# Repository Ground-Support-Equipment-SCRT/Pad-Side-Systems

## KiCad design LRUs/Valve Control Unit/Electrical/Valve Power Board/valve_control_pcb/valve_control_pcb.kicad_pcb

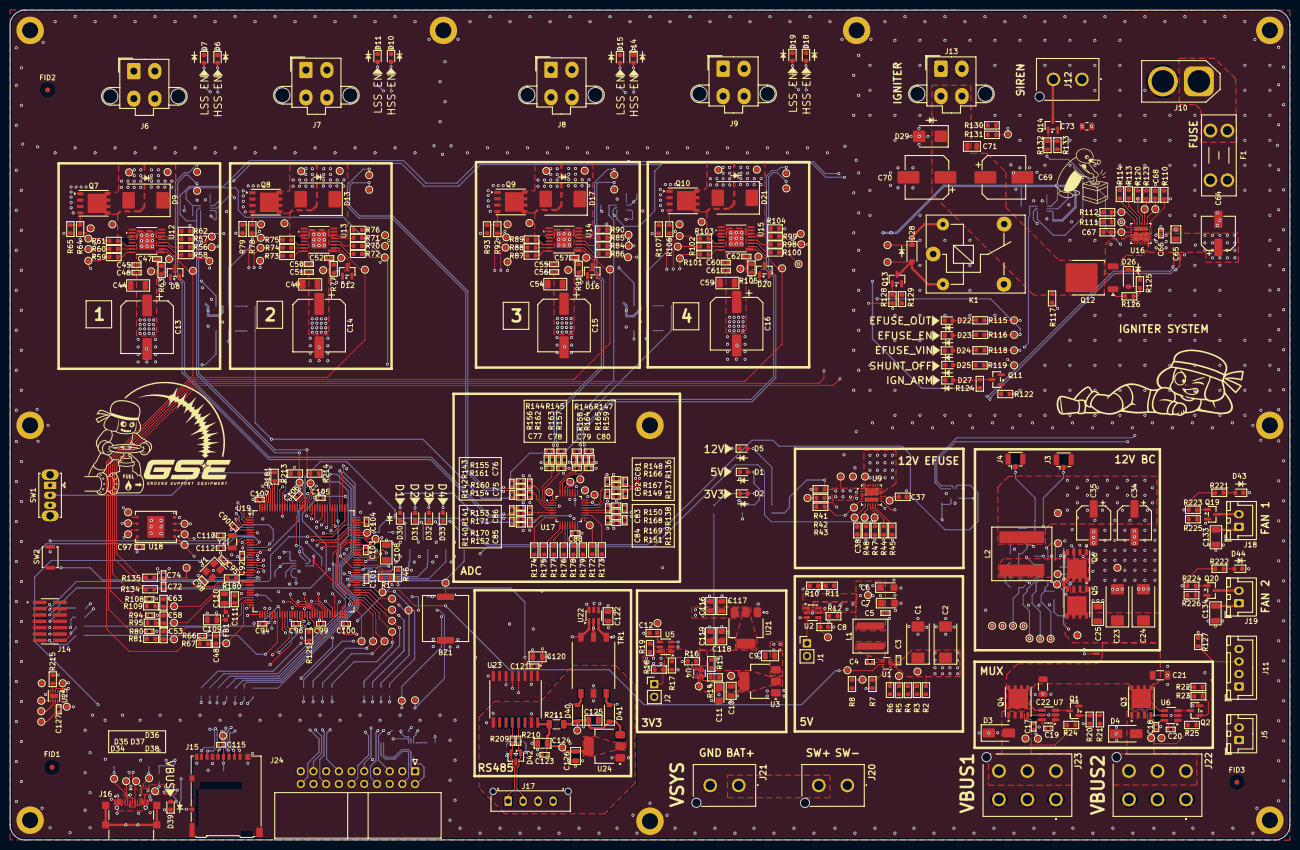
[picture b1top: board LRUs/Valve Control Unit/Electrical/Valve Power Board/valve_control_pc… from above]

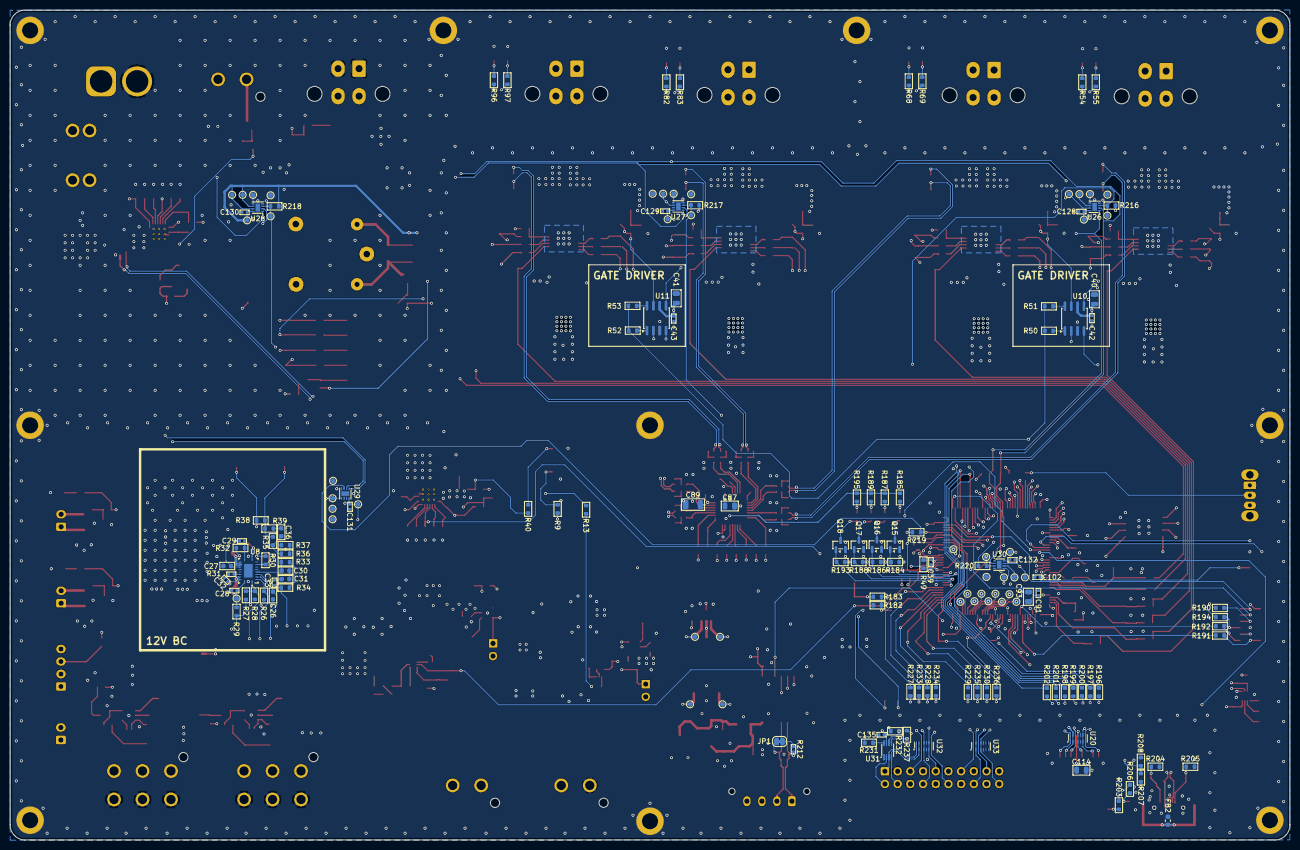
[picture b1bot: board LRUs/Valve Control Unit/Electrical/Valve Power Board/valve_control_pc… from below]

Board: 6 copper layers, 256.0 x 166.0 mm, 719 parts (162 on the bottom side), 374 nets.

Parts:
BZ1: Buzzer; Buzzer_Murata_PKMCS0909E
C1, C2, C23, C24: 10uF; CP_EIA-7343-31_Kemet-D
C3, C4, C5, C17, C18, C19, C20, C28, C32, C39, C42, C43, C45, C46, C47, C50, C51, C52, C55, C56, C57, C60, C61, C62, C66, C72, C74, C75, C76, C77, C78, C79, C80, C81, C82, C83, C84, C85, C86, C88, C90, C91, C92, C94, C96, C97, C99, C100, C101, C102, C103, C104, C105, C106, C107, C115, C121, C123, C127, C128, C129, C130, C131, C132, C135: 100nF; C_0402_1005Metric
C6, C7, C11: 10uF; CP_EIA-3216-18_Kemet-A
C8, C12, C37, C48, C53, C58, C63, C67, C111: 10nF; C_0603_1608Metric
C9, C10, C40, C41, C65, C71, C87, C93, C109, C110, C117, C118, C120: 1uF; C_0805_2012Metric
C13, C14, C15, C16: 120uF; CP_Elec_10x12.6
C21, C22, C25, C44, C49, C54, C59, C89, C108, C133, C134: 4.7uF; C_1206_3216Metric
C26, C38, C68: 47nF; C_0603_1608Metric
C27: 2.2uF; C_0603_1608Metric
C29, C33, C112, C113: 10pF; C_0402_1005Metric
C30, C31, C36: 330pF; C_0603_1608Metric
C34, C35, C64: 47uF; CP_Elec_6.3x5.4
C69, C70: 220uF; CP_Elec_8x10.5
C73, C114, C116, C119, C122, C124, C125, C126: 10uF; C_0805_2012Metric
C95, C98: 20pF; C_0402_1005Metric
D1, D2, D5, D6, D7, D10, D11, D14, D15, D18, D19, D43, D44: RED; LED_0603_1608Metric
D3, D4: SMAJ24A; D_SMA
D8, D12, D16, D20: BAS21; SOT-23
D9, D13, D17, D21: S3M-E3/57T; D_SMC
D22, D23, D24, D25, D27, D30, D31, D32, D33, D39: WHITE; LED_0603_1608Metric
D26: MMSZ5245B; D_SOD-123
D28: 1N4148WS; D_SOD-123
D29: SMBJ20A; D_SMB
D34, D35, D36, D37, D38: ESD441; X2SON2_DPL_TEX
D40, D41: MBR0520LT1G; D_SOD-123
D42: SM712_SOT23; SOT-23
F1: 0297020; Fuseholder_Blade_Mini_Keystone_3568
FB1, FB2: 120R; L_0603_1608Metric
FID1, FID2, FID3: Fiducial; Fiducial_1mm_Mask3mm
H1, H2, H3, H4, H5, H6, H7, H8, H9, H10: MountingHole_Pad; MountingHole_3.2mm_M3_ISO14580_Pad
J1: 01x02_PinHeader; PinHeader_1x02_P2.54mm_Vertical
J2: Conn_01x02_Pin; PinHeader_1x02_P2.54mm_Vertical
J3, J4: Conn_Coaxial; U.FL_Hirose_U.FL-R-SMT-1_Vertical
J5, J18, J19: B2B-XH-A; JST_XH_B2B-XH-A_1x02_P2.50mm_Vertical
J6, J7, J8, J9, J13: 0039299047; Molex_Mini-Fit_Jr_5566-04A2_2x02_P4.20mm_Vertical
J10: XT-60; AMASS_XT60-M_1x02_P7.20mm_Vertical
J11: B4B-XH-A; JST_XH_B4B-XH-A_1x04_P2.50mm_Vertical
J12, J20, J21: 0768290102; 768290102
J14: Conn_ST_STDC14; SAMTEC_FTSH-107-01-X-DV-K
J15: Micro_SD_Card_Det2; microSD_HC_Hirose_DM3AT-SF-PEJM5
J16: GSB1C41110SSHR; AMPHENOL_GSB1C41110SSHR
J17: 0436500415; Molex_Micro-Fit_3.0_43650-0415_1x04_P3.00mm_Vertical
J22, J23: 0768290106; 768290106
J24: IDC-Header_2x10; IDC-Header_2x10_P2.54mm_Horizontal
JP1: SolderJumper_2_Bridged; SolderJumper-2_P1.3mm_Bridged_RoundedPad1.0x1.5mm
K1: J107F1CS205VDC.45; Relay_SPDT_SANYOU_SRD_Series_Form_C
L1: 15uH; L_Coilcraft_XAL6060-XXX
L2: 4.7uH; L_Coilcraft_XAL1010-XXX
NT1, NT2: NetTie_2; NetTie-2_SMD_Pad0.5mm
Q1, Q2, Q11, Q13, Q14, Q15, Q16, Q17, Q18, Q19, Q20: AO3400A; SOT-23
Q3, Q4, Q5, Q6, Q7, Q8, Q9, Q10: SIR5108DP; PowerPAK_SO-8_Single
Q12: STD52P3LLH6; TO-252-2
R1, R16, R125, R129, R132, R184, R186, R188, R193, R225, R226: 47k; R_0603_1608Metric
R2: 220k; R_0603_1608Metric
R3, R14, R26, R30: 20k; R_0603_1608Metric
R4, R47, R120: 9.1k; R_0603_1608Metric
R5, R11: 51k; R_0603_1608Metric
R6, R44, R45, R50, R51, R52, R53, R113, R114, R172, R173, R174, R175, R176, R177, R178, R179, R190, R191, R192, R194, R196, R197, R198, R200, R201, R202, R227, R228, R229, R230, R233, R234, R235, R236: 0; R_0603_1608Metric
R7, R27, R112: 68k; R_0603_1608Metric
R8: 13k; R_0603_1608Metric
R9, R206: 2k; R_0603_1608Metric
R10, R17: 150k; R_0603_1608Metric
R12, R15, R19, R40, R46, R62, R65, R76, R79, R90, R93, R104, R107, R110, R115, R118, R121, R133, R181, R203: 10k; R_0603_1608Metric
R13: 220; R_0603_1608Metric
R18, R21, R23, R24, R25, R43, R117, R131, R207: 100k; R_0603_1608Metric
R20, R22, R49, R122, R134, R135: 1k; R_0603_1608Metric
R28: 8.2k; R_0603_1608Metric
R29: 2; R_0603_1608Metric
R31, R209, R210: 10; R_0402_1005Metric_GSE
R32: 680; R_0603_1608Metric
R33, R48, R64, R78, R92, R106, R123, R126, R128, R183, R223, R224: 100; R_0603_1608Metric
R34: 1.8k; R_0603_1608Metric
R35: 18k; R_0603_1608Metric
R36: 1.2k; R_0603_1608Metric
R37, R39: 75; R_0603_1608Metric
R38: 10; R_0603_1608Metric
R41, R111, R182: 1M; R_0603_1608Metric
R42: 22k; R_0603_1608Metric
R54, R55, R63, R68, R69, R77, R82, R83, R91, R96, R97, R105, R185, R187, R189, R195, R213, R214, R215, R216, R217, R218, R219, R220, R232, R237: 4.7k; R_0603_1608Metric
R56, R57, R58, R59, R60, R61, R67, R70, R71, R72, R73, R74, R75, R81, R84, R85, R86, R87, R88, R89, R95, R98, R99, R100, R101, R102, R103, R109: 15k; R_0603_1608Metric
R66, R80, R94, R108: 680; R_0402_1005Metric_GSE
R116, R119, R124, R127, R221, R222: 2.2k; R_0603_1608Metric
R130: 510k; R_0603_1608Metric
R136, R137, R138, R139, R140, R141, R142, R143, R144, R145, R146, R147: 15k; R_0402_1005Metric_GSE
R148, R149, R150, R151, R152, R153, R154, R155, R156, R157, R158, R159: 90.9k; R_0402_1005Metric_GSE
R160, R161, R162, R163, R164, R165, R166, R167, R168, R169, R170, R171: 1k; R_0402_1005Metric_GSE
R180: 390; R_0603_1608Metric
R199: 22; R_0603_1608Metric
R204, R205: 5.1k; R_0603_1608Metric
R208, R231: 200k; R_0603_1608Metric
R211: 0; R_1206_3216Metric
R212: 120; R_0402_1005Metric_GSE
SW1: SW_SPDT; SW_Slide_SPDT_Straight_CK_OS102011MS2Q
SW2: SW_Push; SW_Push_SPST_NO_Alps_SKRK
TP1, TP2, TP3, TP4, TP5, TP6, TP7, TP8, TP9, TP10, TP11, TP12, TP13, TP14, TP15, TP16, TP17, TP18, TP19, TP20, TP21, TP22, TP23, TP24, TP25, TP26, TP27, TP28, TP29, TP30, TP31, TP32, TP33, TP34, TP35, TP36, TP37, TP38, TP39, TP40, TP41, TP42, TP43, TP44, TP45, TP46, TP47, TP48, TP49, TP50, TP51, TP52, TP53, TP54, TP55, TP56, TP57, TP58, TP59, TP60, TP61, TP62, TP63, TP64, TP65, TP66, TP67, TP68, TP69, TP70, TP71, TP72, TP73, TP74, TP75, TP76, TP77, TP78, TP79, TP80, TP81, TP82, TP83, TP84, TP85, TP86, TP87, TP88, TP89, TP90, TP91, TP92, TP93, TP94, TP95, TP96, TP97, TP98, TP99, TP100, TP101, TP102, TP103, TP104, TP105, TP106, TP107, TP108, TP109, TP110, TP111, TP112, TP113, TP114, TP115, TP116, TP117, TP118, TP119, TP120, TP121, TP122, TP123, TP124, TP125, TP126, TP127, TP128, TP129, TP130, TP131, TP132, TP133, TP134, TP135, TP136, TP137, TP138, TP139, TP140, TP141, TP142, TP143, TP144, TP145, TP146, TP147, TP148, TP149, TP150, TP151, TP152, TP153, TP154, TP155, TP156, TP157, TP158, TP159, TP160, TP161, TP162, TP163, TP164, TP165, TP166, TP167, TP168, TP169, TP170, TP171, TP172, TP173, TP174, TP175, TP176, TP177, TP178, TP179, TP180, TP181, TP182, TP183, TP184, TP185, TP186, TP187, TP188, TP189, TP190, TP191, TP192, TP193, TP194, TP195, TP196, TP197, TP198: TestPoint; TestPoint_Pad_D1.0mm
TR1: 750315371; Transformer_Wuerth_750315371
U1: TPS62933P; SOT-583-8
U2, U5: TPS22810DBV; SOT-23-6
U3, U21: AMS1117-3.3; SOT-223-3_TabPin2
U4: TPS2116DRL; SOT-583-8
U6, U7: LM74700; SOT-23-6_Handsoldering
U8: LM5145RGYR
U9: TPS259830; IC_TPS259830ONRGER
U10, U11: UCC27524D; SOIC-8_3.9x4.9mm_P1.27mm
U12, U13, U14, U15: TPS27SA08CPWPR; TSSOP_CPWPR_TEX
U16: TPS259830ONRGER; IC_TPS259830ONRGER
U17: ADS124S08IPBSR; QFP50P700X700X120-32N
U18: W25Q128JVE; WSON-8-1EP_8x6mm_P1.27mm_EP3.4x4.3mm
U19: STM32L496ZGT6; LQFP-144_20x20mm_P0.5mm
U20, U32, U33: TPD6E05U06RVZ; Texas_R-PUSON-N14
U22: SN6505BDBVR; SOT-23-6
U23: ISO1450BDWR; SOIC127P1030X265-16N
U24: AMS1117-5.0; SOT-223-3_TabPin2
U25, U26, U27, U28, U29, U30: TMP1075DSGR; Texas_DSG0008A_WSON-8-1EP_2x2mm_P0.5mm_EP0.9x1.6mm
U31: PCA9306DC1Z; VSSOP-8_2.3x2mm_P0.5mm
Y1: 8MHz; Crystal_SMD_3225-4Pin_3.2x2.5mm
Y2: 32KHz; Crystal_SMD_3215-2Pin_3.2x1.5mm

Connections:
3V3_EXT: J24.2, U31.2 (VREF1)
3V3_STATUS: R16.2, U4.8 (ST), U19.15 (PF5)
3V3_USB: C118.1, C119.1, U4.6 (VIN2), U21.2 (VO)
5V_MAIN_PG: R1.2, TP1.1 (1_1), U1.7 (PG), U19.89 (PG4)
+3V3: C88.1, C90.1, C92.1, C94.1, C96.1, C97.1, C99.1, C100.1, C101.1, C103.1, C104.1, C105.1, C106.1, C107.1, C108.1, C109.1, C114.1, C115.1, C120.1, C121.1, C127.1, C128.1, C129.1, C130.1, C131.1, C132.1, C135.1, FB1.1, J14.3 (VCC), J15.4 (VDD), R1.1, R19.2, R46.1, R62.1, R76.1, R90.1, R104.1, R121.1, R124.1, R203.1, R213.2, R214.2, R215.2, R216.2, R217.2, R218.2, R219.2, R220.2, R231.2, R232.2, R237.2, SW1.3 (C), TP134.1 (1_1), TP153.1 (1_1), TP155.1 (1_1), TP159.1 (1_1), TP162.1 (1_1), TP165.1 (1_1), TP167.1 (1_1), TP168.1 (1_1), TP171.1 (1_1), TP175.1 (1_1), TP177.1 (1_1), TP179.1 (1_1), TP181.1 (1_1), TP183.1 (1_1), U5.6 (VOUT), U17.15 (IOVDD), U17.16 (DVDD), U18.8 (VCC), U19.6 (VBAT), U19.17 (VDD), U19.39 (VDD), U19.52 (VDD), U19.62 (VDD), U19.72 (VDD), U19.84 (VDD), U19.95 (VDDIO2), U19.106 (VDDUSB), U19.108 (VDD), U19.121 (VDD), U19.131 (VDDIO2), U19.144 (VDD), U23.1 (VCC1), U25.8 (V+), U26.7 (A0), U26.8 (V+), U27.6 (A1), U27.8 (V+), U28.6 (A1), U28.7 (A0), U28.8 (V+), U29.5 (A2), U29.8 (V+), U30.5 (A2), U30.7 (A0), U30.8 (V+), U31.7 (VREF2)
+5V: C40.1, C41.1, C42.1, C43.1, C87.1, C122.1, D28.1 (K), K1.5, R12.2, R185.2, R187.2, R189.2, R195.2, TP108.1 (1_1), TR1.2, U2.6 (VOUT), U10.6 (V_{DD}), U11.6 (V_{DD}), U17.26 (AVDD), U22.2 (VCC), U22.5 (EN)
+12V: C34.1, C35.1, C73.1, C133.1, C134.1, J3.1 (In), J12.1, J18.1, J19.1, L2.2, R38.2, R40.1, R41.2, TP23.1 (1_1), TP24.1 (1_1), U9.1 (IN), U9.2 (IN), U9.3 (IN), U9.16 (IN), U9.25 (IN), U9.27 (EPAD), U9.28 (EPAD), U9.29 (EPAD), U9.30 (EPAD), U9.31 (EPAD), U9.32 (EPAD)
/ADC/AINCOM: TP112.1 (1_1), U17.1 (AINCOM)
/ADC/CLK: R172.2, TP114.1 (1_1), U17.17 (CLK)
/ADC/IGN_VSENSE_DIV_N: R137.1, R149.2, R167.2
/ADC/IGN_VSENSE_DIV_P: R136.1, R148.2, R166.2
/ADC/IGN_VSENSE_FILT_N: C82.1, R167.1, U17.21 (GPIO1/AIN9)
/ADC/IGN_VSENSE_FILT_P: C81.1, R166.1, U17.22 (GPIO0/AIN8)
/ADC/MISO: R178.2, U17.12 (DOUT/~DRDY)
/ADC/MOSI: R177.2, U17.10 (DIN)
/ADC/REFN0: TP110.1 (1_1), U17.29 (REFN0)
/ADC/REFOUT: C89.1, TP115.1 (1_1), U17.23 (REFOUT)
/ADC/REFP0: TP111.1 (1_1), U17.30 (REFP0)
/ADC/SCLK: R176.2, U17.11 (SCLK)
/ADC/START: R174.2, U17.8 (START/SYNC)
/ADC/VALVE1_VSENSE_DIV_N: R141.1, R153.2, R171.2
/ADC/VALVE1_VSENSE_DIV_P: R140.1, R152.2, R170.2
/ADC/VALVE1_VSENSE_FILT_N: C86.1, R171.1, U17.6 (AIN1)
/ADC/VALVE1_VSENSE_FILT_P: C85.1, R170.1, U17.7 (AIN0)
/ADC/VALVE2_VSENSE_DIV_N: R143.1, R155.2, R161.2
/ADC/VALVE2_VSENSE_DIV_P: R142.1, R154.2, R160.2
/ADC/VALVE2_VSENSE_FILT_N: C76.1, R161.1, U17.4 (AIN3)
/ADC/VALVE2_VSENSE_FILT_P: C75.1, R160.1, U17.5 (AIN2)
/ADC/VALVE3_VSENSE_DIV_N: R145.1, R157.2, R163.2
/ADC/VALVE3_VSENSE_DIV_P: R144.1, R156.2, R162.2
/ADC/VALVE3_VSENSE_FILT_N: C78.1, R163.1, U17.2 (AIN5)
/ADC/VALVE3_VSENSE_FILT_P: C77.1, R162.1, U17.3 (AIN4)
/ADC/VALVE4_VSENSE_DIV_N: R147.1, R159.2, R165.2
/ADC/VALVE4_VSENSE_DIV_P: R146.1, R158.2, R164.2
/ADC/VALVE4_VSENSE_FILT_N: C80.1, R165.1, U17.31 (REFN1/AIN7)
/ADC/VALVE4_VSENSE_FILT_P: C79.1, R164.1, U17.32 (REFP1/AIN6)
/ADC/VBUS_VSENSE_DIV_N: R139.1, R151.2, R169.2
/ADC/VBUS_VSENSE_DIV_P: R138.1, R150.2, R168.2
/ADC/VBUS_VSENSE_FILT_N: C84.1, R169.1, U17.19 (GPIO3/AIN11)
/ADC/VBUS_VSENSE_FILT_P: C83.1, R168.1, U17.20 (GPIO2/AIN10)
/ADC/~CS: R175.2, U17.9 (~CS)
/ADC/~DRDY: R179.2, U17.13 (~DRDY)
/ADC/~RESET: R173.2, U17.18 (~RESET)
/Connectors/I2C_SLAVE_SCL: J24.1, U31.3 (SCL1), U32.14 (D1+)
/Connectors/I2C_SLAVE_SDA: J24.4, U31.4 (SDA1), U32.13 (D1-)
/Connectors/PIN5: J24.5, R227.1, U32.12 (D2+)
/Connectors/PIN8: J24.8, R233.2, U32.11 (D2-)
/Connectors/PIN9: J24.9, R228.1, U32.9 (D3+)
/Connectors/PIN12: J24.12, R234.2, U32.8 (D3-)
/Connectors/PIN13: J24.13, R229.1, U33.14 (D1+)
/Connectors/PIN16: J24.16, R235.2, U33.13 (D1-)
/Connectors/PIN17: J24.17, R230.1, U33.12 (D2+)
/Connectors/PIN20: J24.20, R236.2, U33.11 (D2-)
/Connectors/VSYS_BAT+: J20.2, J21.1
/Igniter/DVDT: C67.1, TP102.1 (1_1), U16.15 (DVDT/BGATE)
/Igniter/EFUSE_OVLO: R111.1, R112.1, TP99.1 (1_1), U16.12 (OVLO)
/Igniter/IGNITER+: D26.1 (K), Q12.3 (S), R115.1, R125.2, R132.1, TP101.1 (1_1), U16.17 (OUT), U16.18 (OUT), U16.19 (OUT), U16.20 (OUT), U16.21 (OUT), U16.22 (OUT), U16.23 (OUT), U16.24 (OUT)
/Igniter/IGN_ARM: D26.2 (A), J11.1, J11.4, R122.2, R125.1, R126.2
/Igniter/IGN_RLY-: D28.2 (A), K1.2, Q13.3 (D), TP109.1 (1_1)
/Igniter/ILIM: R123.2, TP104.1 (1_1), U16.8 (ILIM)
/Igniter/IMON_IC: R120.2, R135.2, U16.9 (IMON)
/Igniter/ITIM: C68.1, TP106.1 (1_1), U16.7 (ITIMER)
/Igniter/SENSE: R130.1, R131.2, R134.2, TP107.1 (1_1)
/RS-485/5V_ISO: C125.1, D40.1 (K), D41.1 (K), R211.2, TP145.1 (1_1), U24.3 (VI)
/RS-485/5V_ISO_FILT: C123.1, C124.1, C126.1, R211.1, TP146.1 (1_1), U23.16 (VCC2), U24.2 (VO)
/RS-485/A1: TP141.1 (1_1), TR1.3, U22.1 (D1)
/RS-485/A2: TP142.1 (1_1), TR1.1, U22.3 (D2)
/RS-485/A_RX_MAIN_N: R210.2, U23.13 (B)
/RS-485/A_RX_MAIN_P: R209.2, U23.12 (A)
/RS-485/B1: D40.2 (A), TP143.1 (1_1), TR1.4
/RS-485/B2: D41.2 (A), TP144.1 (1_1), TR1.6
/RS-485/RX_MAIN_N: D42.1 (A1), J17.2, JP1.1 (A), R210.1
/RS-485/RX_MAIN_P: D42.2 (A2), J17.1, R209.1, R212.2
/STM32/BOOT: R181.1, U19.138 (PH3)
/STM32/D1: Q15.1 (G), R184.1, U19.86 (PD15)
/STM32/D2: Q16.1 (G), R186.1, U19.85 (PD14)
/STM32/D3: Q17.1 (G), R188.1, U19.82 (PD13)
/STM32/D4: Q18.1 (G), R193.1, U19.81 (PD12)
/STM32/JTDI: J14.10 (JTDI/NC), R194.1
/STM32/JTDI_STM32: R194.2, U19.110 (SYS_JTDI)
/STM32/JTDO: J14.8 (JTDO/SWO), R190.1
/STM32/NRST: C102.2, J14.12 (~RST), SW2.2, U19.25 (NRST)
/STM32/QUADSPI_BK1_IO0: TP118.1 (1_1), U18.5 (DI/IO_{0}), U19.20 (QUADSPI_BK1_IO0)
/STM32/QUADSPI_BK1_IO1: TP119.1 (1_1), U18.2 (DO/IO_{1}), U19.21 (QUADSPI_BK1_IO1)
/STM32/QUADSPI_BK1_IO2: TP117.1 (1_1), U18.3 (~WP/IO_{2}), U19.19 (QUADSPI_BK1_IO2)
/STM32/QUADSPI_BK1_IO3: TP116.1 (1_1), U18.7 (~HOLD/~RESET/IO_{3}), U19.18 (QUADSPI_BK1_IO3)
/STM32/QUADSPI_CLK: TP120.1 (1_1), U18.6 (CLK), U19.22 (QUADSPI_CLK)
/STM32/SWCLK: J14.6 (JCLK/SWCLK), U19.109 (SYS_JTCK-SWCLK)
/STM32/SWDIO: J14.4 (JTMS/SWDIO), U19.105 (SYS_JTMS-SWDIO)
/STM32/VDDA: C110.1, C111.1, FB1.2, U19.33 (VDDA)
/STM32/~QUADSPI_BK1_NCS: TP121.1 (1_1), U18.1 (~CS), U19.36 (QUADSPI_BK1_NCS)
/System Power/LDO 3V3/VIN: C5.1, C6.1, C7.1, C9.1, L1.2, R7.1, R9.2, R10.2, TP4.1 (1_1), U2.1 (VIN), U3.3 (VI)
/System Power/LDO 3V3/VOUT: C10.1, C11.1, R13.1, R14.2, TP7.1 (1_1), U3.2 (VO), U4.3 (VIN1), U4.5 (MODE)
/System Power/LSW 3V3/CT: C12.1, TP9.1 (1_1), U5.4 (CT)
/System Power/LSW 3V3/EN_UVLO: J2.1, R17.1, R18.2, U5.3 (EN/UVLO)
/System Power/LSW 3V3/QOD: R19.1, U5.5 (QOD)
/System Power/LSW 3V3/VIN: R16.1, R17.2, TP8.1 (1_1), U4.2 (VOUT), U4.7 (VOUT), U5.1 (VIN)
/System Power/LSW 5V/CT: C8.1, TP6.1 (1_1), U2.4 (CT)
/System Power/LSW 5V/EN_UVLO: J1.1, R10.1, R11.1, U2.3 (EN/UVLO)
/System Power/LSW 5V/QOD: R12.1, U2.5 (QOD)
/System Power/MUX 3V3/PR1: R14.1, R15.1, U4.4 (PR1)
/System Power/System 5V/BST: C4.1, U1.6 (BST)
/System Power/System 5V/FB: R7.2, R8.1, TP5.1 (1_1), U1.8 (FB)
/System Power/System 5V/RT: R6.2, U1.1 (RT)
/System Power/System 5V/SW: C4.2, L1.1, U1.5 (SW)
/System Power/System 5V/VEN: R4.1, R5.1, TP3.1 (1_1), U1.2 (EN)
/USB-C/V5P0_USB: C116.1, C117.1, D38.1 (K), J16.A4_B9 (VBUS_A), J16.B4_A9 (VBUS_B), R206.2, R207.2, TP135.1 (1_1), U21.3 (VI)
/Valves/12V_VALVES: C13.1, C14.1, C15.1, C16.1, C44.1, C45.1, C46.1, C47.1, C49.1, C50.1, C51.1, C52.1, C54.1, C55.1, C56.1, C57.1, C59.1, C60.1, C61.1, C62.1, TP32.1 (1_1), TP33.1 (1_1), TP49.1 (1_1), TP65.1 (1_1), TP81.1 (1_1), U9.17 (OUT), U9.18 (OUT), U9.19 (OUT), U9.20 (OUT), U9.21 (OUT), U9.22 (OUT), U9.23 (OUT), U9.24 (OUT), U12.EPAD (VBB), U13.EPAD (VBB), U14.EPAD (VBB), U15.EPAD (VBB)
/Valves/12V_main/BST: R31.2, U8.17 (BST)
/Valves/12V_main/COMP: C31.2, C33.1, TP17.1 (1_1), U8.4 (COMP)
/Valves/12V_main/EN_UVLO: R27.1, R28.2, TP14.1 (1_1), U8.1 (EN_UVLO)
/Valves/12V_main/FB: C30.1, C36.2, R33.1, R35.1, R36.2, TP20.1 (1_1), U8.5 (FB)
/Valves/12V_main/HO: Q5.4 (G), U8.18 (HO)
/Valves/12V_main/ILIM: C29.1, R32.2, U8.11 (ILIM)
/Valves/12V_main/LO: Q6.4 (G), U8.13 (LO)
/Valves/12V_main/RT: R26.2, TP12.1 (1_1), U8.2 (RT)
/Valves/12V_main/SENSE_OUT: J4.1 (In), R35.2, R38.1, R39.2
/Valves/12V_main/SS_TRK: C26.1, TP13.1 (1_1), U8.3 (SS_TRK)
/Valves/12V_main/SW: C32.2, L2.1, Q5.1 (S), Q5.2 (S), Q5.3 (S), Q6.5 (D), R32.1, TP21.1 (1_1), U8.19 (SW)
/Valves/12V_main/SYNCIN: R30.2, TP15.1 (1_1), U8.8 (SYNCIN)
/Valves/12V_main/VCC: C27.1, R30.1, U8.14 (VCC)
/Valves/12V_main/VIN_S: C28.1, R29.1, TP16.1 (1_1), U8.20 (VIN)
/Valves/Gate Drivers/OUTA1: R69.2, R78.2, TP51.1 (1_1), U10.7 (OUTA)
/Valves/Gate Drivers/OUTA2: R97.2, R106.2, TP83.1 (1_1), U11.7 (OUTA)
/Valves/Gate Drivers/OUTB1: R55.2, R64.2, TP35.1 (1_1), U10.5 (OUTB)
/Valves/Gate Drivers/OUTB2: R83.2, R92.2, TP67.1 (1_1), U11.5 (OUTB)
/Valves/Valve 1/12V_OUT+: D9.1 (K), J6.4, TP44.1 (1_1), U12.6 (VOUT), U12.7 (VOUT), U12.8 (VOUT), U12.9 (VOUT), U12.10 (VOUT), U12.11 (VOUT)
/Valves/Valve 1/12V_OUT-: D9.2 (A), J6.3, Q7.5 (D), TP45.1 (1_1)
/Valves/Valve 1/LFET_GATE: Q7.4 (G), R64.1, R65.1
/Valves/Valve 1/LSW_DIA_EN_PROT: R59.1, U12.16 (DIA_EN)
/Valves/Valve 1/LSW_LATCH_PROT: R58.1, U12.3 (LATCH)
/Valves/Valve 1/LSW_SEL1_PROT: R61.1, U12.14 (SEL1)
/Valves/Valve 1/LSW_SEL2_PROT: R60.1, U12.15 (SEL2)
/Valves/Valve 1/LSW_SNS_PROT: R66.2, R67.2, TP43.1 (1_1), U12.2 (SNS)
/Valves/Valve 1/MODGND: C47.2, D8.3 (K), R63.2, TP41.1 (1_1), U12.1 (GND)
/Valves/Valve 1/~LSW_ST_PROT: R57.1, R62.2, U12.5 (~ST)
/Valves/Valve 2/12V_OUT+: D13.1 (K), J7.4, TP60.1 (1_1), U13.6 (VOUT), U13.7 (VOUT), U13.8 (VOUT), U13.9 (VOUT), U13.10 (VOUT), U13.11 (VOUT)
/Valves/Valve 2/12V_OUT-: D13.2 (A), J7.3, Q8.5 (D), TP61.1 (1_1)
/Valves/Valve 2/LFET_GATE: Q8.4 (G), R78.1, R79.1
/Valves/Valve 2/LSW_DIA_EN_PROT: R73.1, U13.16 (DIA_EN)
/Valves/Valve 2/LSW_LATCH_PROT: R72.1, U13.3 (LATCH)
/Valves/Valve 2/LSW_SEL1_PROT: R75.1, U13.14 (SEL1)
/Valves/Valve 2/LSW_SEL2_PROT: R74.1, U13.15 (SEL2)
/Valves/Valve 2/LSW_SNS_PROT: R80.2, R81.2, TP59.1 (1_1), U13.2 (SNS)
/Valves/Valve 2/MODGND: C52.2, D12.3 (K), R77.2, TP57.1 (1_1), U13.1 (GND)
/Valves/Valve 2/~LSW_ST_PROT: R71.1, R76.2, U13.5 (~ST)
/Valves/Valve 3/12V_OUT+: D17.1 (K), J8.4, TP76.1 (1_1), U14.6 (VOUT), U14.7 (VOUT), U14.8 (VOUT), U14.9 (VOUT), U14.10 (VOUT), U14.11 (VOUT)
/Valves/Valve 3/12V_OUT-: D17.2 (A), J8.3, Q9.5 (D), TP77.1 (1_1)
/Valves/Valve 3/LFET_GATE: Q9.4 (G), R92.1, R93.1
/Valves/Valve 3/LSW_DIA_EN_PROT: R87.1, U14.16 (DIA_EN)
/Valves/Valve 3/LSW_LATCH_PROT: R86.1, U14.3 (LATCH)
/Valves/Valve 3/LSW_SEL1_PROT: R89.1, U14.14 (SEL1)
/Valves/Valve 3/LSW_SEL2_PROT: R88.1, U14.15 (SEL2)
/Valves/Valve 3/LSW_SNS_PROT: R94.2, R95.2, TP75.1 (1_1), U14.2 (SNS)
/Valves/Valve 3/MODGND: C57.2, D16.3 (K), R91.2, TP73.1 (1_1), U14.1 (GND)
/Valves/Valve 3/~LSW_ST_PROT: R85.1, R90.2, U14.5 (~ST)
/Valves/Valve 4/12V_OUT+: D21.1 (K), J9.4, TP92.1 (1_1), U15.6 (VOUT), U15.7 (VOUT), U15.8 (VOUT), U15.9 (VOUT), U15.10 (VOUT), U15.11 (VOUT)
/Valves/Valve 4/12V_OUT-: D21.2 (A), J9.3, Q10.5 (D), TP93.1 (1_1)
/Valves/Valve 4/LFET_GATE: Q10.4 (G), R106.1, R107.1
/Valves/Valve 4/LSW_DIA_EN_PROT: R101.1, U15.16 (DIA_EN)
/Valves/Valve 4/LSW_LATCH_PROT: R100.1, U15.3 (LATCH)
/Valves/Valve 4/LSW_SEL1_PROT: R103.1, U15.14 (SEL1)
/Valves/Valve 4/LSW_SEL2_PROT: R102.1, U15.15 (SEL2)
/Valves/Valve 4/LSW_SNS_PROT: R108.2, R109.2, TP91.1 (1_1), U15.2 (SNS)
/Valves/Valve 4/MODGND: C62.2, D20.3 (K), R105.2, TP89.1 (1_1), U15.1 (GND)
/Valves/Valve 4/~LSW_ST_PROT: R99.1, R104.2, U15.5 (~ST)
/Valves/input_mux/VIN1_DIS_GATE: Q1.1 (G), R20.1, R21.2
/Valves/input_mux/VIN1_GATE: Q4.4 (G), U7.5 (GATE)
/Valves/input_mux/VIN2_DIS_GATE: Q2.1 (G), R22.1, R23.2
/Valves/input_mux/VIN2_GATE: Q3.4 (G), U6.5 (GATE)
/Valves/input_mux/~VIN1_SHDN: Q1.3 (D), R24.1, U7.3 (EN)
/Valves/input_mux/~VIN2_SHDN: Q2.3 (D), R25.1, U6.3 (EN)
/Valves/master_efuse/DVDT: C37.1, TP28.1 (1_1), U9.15 (DVDT/BGATE)
/Valves/master_efuse/ILIM: R48.2, TP31.1 (1_1), U9.8 (ILIM)
/Valves/master_efuse/IMON_IC: R47.2, R49.2, TP30.1 (1_1), U9.9 (IMON)
/Valves/master_efuse/ITIM: C38.1, TP29.1 (1_1), U9.7 (ITIMER)
ADC_MISO: R178.1, U19.42 (SPI1_MISO)
ADC_MOSI: R177.1, U19.43 (SPI1_MOSI)
ADC_SCLK: R176.1, U19.41 (PA5)
ADC_START: R174.1, U19.49 (PF11)
CONTINUITY_SENSE: C72.1, R134.1, U19.27 (PC1)
D_N: D35.1 (K), J16.A7 (DN1), J16.B7 (DN2), TP139.1 (1_1), U19.103 (USB_OTG_FS_DM)
D_P: D37.1 (K), J16.A6 (DP1), J16.B6 (DP2), TP140.1 (1_1), U19.104 (USB_OTG_FS_DP)
EFUSE_IMON: C39.1, R49.1, U19.91 (PG6)
EFUSE_PG: R46.2, U9.13 (PG), U19.90 (PG5)
FAN1_TOGGLE: R221.1, R223.1, U19.13 (PF3)
FAN2_TOGGLE: R222.1, R224.1, U19.12 (PF2)
GND: BZ1.2 (-), C1.2, C2.2, C3.2, C5.2, C6.2, C7.2, C8.2, C9.2, C10.2, C11.2, C12.2, C13.2, C14.2, C15.2, C16.2, C17.2, C18.2, C21.2, C22.2, C23.2, C24.2, C25.2, C26.2, C27.2, C28.2, C29.2, C34.2, C35.2, C37.2, C38.2, C39.2, C40.2, C41.2, C42.2, C43.2, C44.2, C45.2, C46.2, C48.2, C49.2, C50.2, C51.2, C53.2, C54.2, C55.2, C56.2, C58.2, C59.2, C60.2, C61.2, C63.2, C64.2, C65.2, C66.2, C67.2, C68.2, C69.2, C70.2, C71.2, C72.2, C73.2, C74.2, C75.2, C76.2, C77.2, C78.2, C79.2, C80.2, C81.2, C82.2, C83.2, C84.2, C85.2, C86.2, C87.2, C88.2, C89.2, C90.2, C91.2, C92.2, C93.2, C94.2, C95.2, C96.2, C97.2, C98.2, C99.2, C100.2, C101.2, C102.1, C103.2, C104.2, C105.2, C106.2, C107.2, C108.2, C109.2, C110.2, C111.2, C112.2, C113.2, C114.2, C115.2, C116.2, C117.2, C118.2, C119.2, C120.2, C121.2, C122.2, C127.2, C128.2, C129.2, C130.2, C131.2, C132.2, C133.2, C134.2, C135.2, D1.1 (K), D2.1 (K), D3.1 (K), D4.1 (K), D5.1 (K), D6.1 (K), D7.1 (K), D8.1 (A), D10.1 (K), D11.1 (K), D12.1 (A), D14.1 (K), D15.1 (K), D16.1 (A), D18.1 (K), D19.1 (K), D20.1 (A), D22.1 (K), D23.1 (K), D24.1 (K), D25.1 (K), D27.1 (K), D29.2 (A), D34.2 (A), D35.2 (A), D36.2 (A), D37.2 (A), D38.2 (A), D39.1 (K), D43.1 (K), D44.1 (K), FB2.2, H1.1 (1_1), H2.1 (1_1), H3.1 (1_1), H4.1 (1_1), H5.1 (1_1), H6.1 (1_1), H7.1 (1_1), H8.1 (1_1), H9.1 (1_1), H10.1 (1_1), J1.2, J2.2, J3.2 (Ext), J4.2 (Ext), J10.2, J11.2, J13.1, J13.2, J14.5 (GND), J14.7 (GND), J14.11 (GNDDetect), J15.6 (VSS), J15.9 (DET_B), J15.SH (SHIELD), J16.A1_B12 (GND_A), J16.B1_A12 (GND_B), J21.2, J22.1, J22.2, J22.3, J23.1, J23.2, J23.3, J24.3, J24.6, J24.7, J24.10, J24.11, J24.14, J24.15, J24.18, J24.19, K1.1, K1.3, NT1.1, NT2.1, Q1.2 (S), Q2.2 (S), Q6.1 (S), Q6.2 (S), Q6.3 (S), Q7.1 (S), Q7.2 (S), Q7.3 (S), Q8.1 (S), Q8.2 (S), Q8.3 (S), Q9.1 (S), Q9.2 (S), Q9.3 (S), Q10.1 (S), Q10.2 (S), Q10.3 (S), Q11.2 (S), Q13.2 (S), Q14.2 (S), Q15.2 (S), Q16.2 (S), Q17.2 (S), Q18.2 (S), Q19.2 (S), Q20.2 (S), R5.2, R6.1, R8.2, R11.2, R15.2, R18.1, R21.1, R23.1, R26.1, R28.1, R37.1, R43.1, R44.1, R45.1, R47.1, R48.1, R63.1, R65.2, R66.1, R77.1, R79.2, R80.1, R91.1, R93.2, R94.1, R105.1, R107.2, R108.1, R110.2, R112.2, R113.1, R114.1, R120.1, R123.1, R129.2, R131.1, R133.2, R148.1, R149.1, R150.1, R151.1, R152.1, R153.1, R154.1, R155.1, R156.1, R157.1, R158.1, R159.1, R172.1, R182.1, R184.2, R186.2, R188.2, R193.2, R204.2, R205.2, R208.1, R225.2, R226.2, SW1.1 (A), SW2.1, TP18.1 (1_1), TP19.1 (1_1), TP27.1 (1_1), TP42.1 (1_1), TP58.1 (1_1), TP74.1 (1_1), TP90.1 (1_1), TP113.1 (1_1), TP149.1 (1_1), TP150.1 (1_1), TP151.1 (1_1), TP152.1 (1_1), TP156.1 (1_1), TP157.1 (1_1), TP158.1 (1_1), TP161.1 (1_1), TP163.1 (1_1), TP164.1 (1_1), TP169.1 (1_1), TP170.1 (1_1), TP173.1 (1_1), TP174.1 (1_1), TP176.1 (1_1), TP180.1 (1_1), TP182.1 (1_1), TP186.1 (1_1), TP188.1 (1_1), U1.4 (GND), U2.2 (GND), U3.1 (GND), U4.1 (GND), U5.2 (GND), U6.2 (GND), U7.2 (GND), U8.6 (AGND), U8.12 (PGND), U8.15 (EP), U8.21 (EP), U9.4 (GND), U9.5 (GND), U9.14 (GND), U9.26 (GND), U9.33 (EPAD), U9.34 (EPAD), U9.35 (EPAD), U10.3 (GND), U11.3 (GND), U16.4 (GND), U16.5 (GND), U16.14 (GND), U16.26 (GND), U16.33 (EPAD), U16.34 (EPAD), U16.35 (EPAD), U17.14 (DGND), U17.24 (REFCOM), U17.27 (AVSS), U17.28 (AVSS-SW), U18.4 (GND), U18.9 (EP), U19.16 (VSS), U19.30 (VSSA), U19.31 (VREF-), U19.38 (VSS), U19.51 (VSS), U19.61 (VSS), U19.71 (VSS), U19.83 (VSS), U19.94 (VSS), U19.107 (VSS), U19.120 (VSS), U19.130 (VSS), U19.143 (VSS), U20.5 (GND), U20.10 (GND), U21.1 (GND), U22.4 (GND), U22.6 (CLK), U23.2 (GND1), U23.8 (GND1__1), U25.4 (GND), U25.5 (A2), U25.6 (A1), U25.7 (A0), U25.9 (EP), U26.4 (GND), U26.5 (A2), U26.6 (A1), U26.9 (EP), U27.4 (GND), U27.5 (A2), U27.7 (A0), U27.9 (EP), U28.4 (GND), U28.5 (A2), U28.9 (EP), U29.4 (GND), U29.6 (A1), U29.7 (A0), U29.9 (EP), U30.4 (GND), U30.6 (A1), U30.9 (EP), U31.1 (GND), U32.5 (GND), U32.10 (GND), U33.5 (GND), U33.10 (GND), Y1.2, Y1.4
I2C1_SCL: R213.1, TP148.1 (1_1), U19.129 (I2C1_SCL), U25.2 (SCL), U26.2 (SCL), U27.2 (SCL), U28.2 (SCL), U29.2 (SCL), U30.2 (SCL)
I2C1_SDA: R214.1, TP147.1 (1_1), U19.128 (I2C1_SDA), U25.1 (SDA), U26.1 (SDA), U27.1 (SDA), U28.1 (SDA), U29.1 (SDA), U30.1 (SDA)
I2C3_SCL: R232.1, TP197.1 (1_1), U19.92 (I2C3_SCL), U31.6 (SCL2)
I2C3_SDA: R237.1, TP198.1 (1_1), U19.93 (I2C3_SDA), U31.5 (SDA2)
IGNITER_FIRE: R110.1, R116.1, TP98.1 (1_1), U16.6 (EN/UVLO), U19.54 (PF14)
IGN_VSENSE_N: NT2.2, R137.2
IGN_VSENSE_P: C64.1, C65.1, C66.1, F1.2, R111.2, R117.2, R118.1, R127.1, R136.2, TP97.1 (1_1), U16.1 (IN), U16.2 (IN), U16.3 (IN), U16.16 (IN), U16.25 (IN), U16.27 (EPAD), U16.28 (EPAD), U16.29 (EPAD), U16.30 (EPAD), U16.31 (EPAD), U16.32 (EPAD)
IMON: C74.1, R135.1, TP105.1 (1_1), U19.26 (PC0)
ISOGND: C123.2, C124.2, C125.2, C126.2, D42.3 (common), J17.3, TR1.5, U23.9 (GND2), U23.15 (GND2__1), U24.1 (GND)
MAIN_DE: U19.47 (LPUART1_DE), U23.6 (D)
MAIN_RX: R192.1, U19.45 (USART3_RX), U23.3 (R)
MAIN_TX: R191.1, U19.44 (USART3_TX), U23.5 (DE)
unnamed: BZ1.1 (+), R183.1, TP133.1 (1_1)
unnamed: C30.2, C31.1
unnamed: C32.1, R31.1
unnamed: C33.2, R34.2, TP22.1 (1_1)
unnamed: C36.1, R39.1
unnamed: C98.1, R180.2, Y1.3
unnamed: D1.2 (A), R9.1
unnamed: D2.2 (A), R13.2
unnamed: D5.2 (A), R40.2
unnamed: D6.2 (A), R54.1
unnamed: D7.2 (A), R55.1
unnamed: D10.2 (A), R68.1
unnamed: D11.2 (A), R69.1
unnamed: D14.2 (A), R82.1
unnamed: D15.2 (A), R83.1
unnamed: D18.2 (A), R96.1
unnamed: D19.2 (A), R97.1
unnamed: D22.2 (A), R115.2
unnamed: D23.2 (A), R116.2
unnamed: D24.2 (A), R118.2
unnamed: D25.2 (A), R119.2
unnamed: D27.2 (A), Q11.3 (D), R124.2
unnamed: C69.1, C70.1, C71.1, D29.1 (K), J13.3, J13.4, K1.4, Q12.2 (D), R117.1, R130.2
unnamed: D30.2 (A), R185.1
unnamed: D30.1 (K), Q15.3 (D)
unnamed: D31.2 (A), R187.1
unnamed: D31.1 (K), Q16.3 (D)
unnamed: D32.2 (A), R189.1
unnamed: D32.1 (K), Q17.3 (D)
unnamed: D33.2 (A), R195.1
unnamed: D33.1 (K), Q18.3 (D)
unnamed: D34.1 (K), J16.A5 (CC1), R205.1, TP136.1 (1_1)
unnamed: D36.1 (K), J16.B5 (CC2), R204.1, TP137.1 (1_1)
unnamed: D39.2 (A), R206.1
unnamed: D43.2 (A), R221.2
unnamed: D44.2 (A), R222.2
unnamed: J5.1, R41.1
unnamed: J5.2, R42.2, TP25.1 (1_1), U9.6 (EN/UVLO)
unnamed: F1.1, J10.1
unnamed: J11.3, R127.2
unnamed: J12.2, Q14.3 (D)
unnamed: J14.13 (VCP_RX), R191.2
unnamed: J14.14 (VCP_TX), R192.2
unnamed: J15.5 (CLK), R199.2, U20.11 (D2-)
unnamed: J15.3 (CMD), R198.1, U20.12 (D2+)
unnamed: J15.7 (DAT0), R200.1, U20.9 (D3+)
unnamed: J15.8 (DAT1), R197.1, U20.8 (D3-)
unnamed: J15.1 (DAT2), R202.1, U20.14 (D1+)
unnamed: J15.2 (DAT3/CD), R201.1, U20.13 (D1-)
unnamed: J15.10 (DET_A), R196.1, R203.2
unnamed: FB2.1, J16.SH1 (SHIELD), J16.SH2 (SHIELD__1), J16.SH3 (SHIELD__2), J16.SH4 (SHIELD__3)
unnamed: J18.2, Q19.3 (D)
unnamed: J19.2, Q20.3 (D)
unnamed: JP1.2 (B), R212.1
unnamed: Q11.1 (G), R122.1
unnamed: Q12.1 (G), R126.1
unnamed: Q13.1 (G), R128.1, R129.1
unnamed: Q14.1 (G), R132.2, R133.1
unnamed: Q19.1 (G), R223.2, R225.1
unnamed: Q20.1 (G), R224.2, R226.1
unnamed: R2.1, R3.2
unnamed: R3.1, R4.2
unnamed: R33.2, R34.1
unnamed: R36.1, R37.2
unnamed: R181.2, SW1.2 (B)
unnamed: C20.2, U6.1 (VCAP)
unnamed: C19.2, U7.1 (VCAP)
unnamed: R45.2, U9.11 (NRETRY)
unnamed: R42.1, R43.2, TP26.1 (1_1), U9.12 (OVLO)
unnamed: R44.2, U9.10 (RETRY_DLY)
unnamed: R50.1, U10.1 (ENA)
unnamed: R51.1, U10.8 (ENB)
unnamed: R52.1, U11.1 (ENA)
unnamed: R53.1, U11.8 (ENB)
unnamed: R56.1, U12.4 (EN)
unnamed: R70.1, U13.4 (EN)
unnamed: R84.1, U14.4 (EN)
unnamed: R98.1, U15.4 (EN)
unnamed: R114.2, U16.11 (NRETRY)
unnamed: R113.2, U16.10 (RETRY_DLY)
unnamed: R182.2, R183.2, TP132.1 (1_1), U19.69 (PB10)
unnamed: TP131.1 (1_1), U19.96 (PC6)
unnamed: C113.1, U19.8 (RCC_OSC32_IN), Y2.1
unnamed: C112.1, U19.9 (RCC_OSC32_OUT), Y2.2
unnamed: TP122.1 (1_1), U19.58 (PE7)
unnamed: TP123.1 (1_1), U19.59 (PE8)
unnamed: TP124.1 (1_1), U19.60 (PE9)
unnamed: TP125.1 (1_1), U19.63 (PE10)
unnamed: TP126.1 (1_1), U19.64 (PE11)
unnamed: TP127.1 (1_1), U19.65 (PE12)
unnamed: TP128.1 (1_1), U19.66 (PE13)
unnamed: TP129.1 (1_1), U19.67 (PE14)
unnamed: TP130.1 (1_1), U19.68 (PE15)
unnamed: C95.1, U19.23 (RCC_OSC_IN), Y1.1
unnamed: R180.1, U19.24 (RCC_OSC_OUT)
unnamed: C91.1, C93.1, U19.32 (VREF+)
unnamed: R231.1, U31.8 (EN)
PGOOD_IGNITER: R121.2, TP103.1 (1_1), U16.13 (PG), U19.53 (PF13)
PIN5_STM32: R227.2, TP189.1 (1_1), U19.80 (PD11)
PIN8_STM32: R233.1, TP193.1 (1_1), U19.79 (PD10)
PIN9_STM32: R228.2, TP190.1 (1_1), U19.78 (PD9)
PIN12_STM32: R234.1, TP194.1 (1_1), U19.77 (PD8)
PIN13_STM32: R229.2, TP191.1 (1_1), U19.76 (PB15)
PIN16_STM32: R235.1, TP195.1 (1_1), U19.75 (PB14)
PIN17_STM32: R230.2, TP192.1 (1_1), U19.74 (PB13)
PIN20_STM32: R236.1, TP196.1 (1_1), U19.73 (PB12)
SDMMC1_CK: R199.1, U19.113 (SDMMC1_CK)
SDMMC1_CMD: R198.2, U19.116 (PD2)
SDMMC1_D0: R200.2, U19.98 (SDMMC1_D0)
SDMMC1_D1: R197.2, U19.99 (SDMMC1_D1)
SDMMC1_D2: R202.2, U19.111 (SDMMC1_D2)
SDMMC1_D3: R201.2, U19.112 (SDMMC1_D3)
SD_DET: R196.2, U19.97 (PC7)
SHUNT_DISABLE: R119.1, R128.2, TP100.1 (1_1), U19.55 (PF15)
TEMP_ALERT1: R215.1, TP154.1 (1_1), U19.37 (PA3), U25.3 (ALERT)
TEMP_ALERT2: R216.1, TP160.1 (1_1), U19.88 (PG3), U26.3 (ALERT)
TEMP_ALERT3: R217.1, TP166.1 (1_1), U19.87 (PG2), U27.3 (ALERT)
TEMP_ALERT4: R218.1, TP172.1 (1_1), U19.100 (PA8), U28.3 (ALERT)
TEMP_ALERT5: R219.1, TP178.1 (1_1), U19.102 (PA10), U29.3 (ALERT)
TEMP_ALERT6: R220.1, TP184.1 (1_1), U19.70 (PB11), U30.3 (ALERT)
USB_VBUS_DET: R207.1, R208.2, TP138.1 (1_1), U19.101 (USB_OTG_FS_VBUS)
V-12P0_MAIN_PG: TP11.1 (1_1), U8.10 (PGOOD), U19.14 (PF4)
VALVE1.LSW_DIA_EN: R59.2, TP38.1 (1_1), U19.11 (PF1)
VALVE1.LSW_LATCH: R58.2, TP37.1 (1_1), U19.2 (PE3)
VALVE1.LSW_SEL1: R61.2, TP40.1 (1_1), U19.5 (PE6)
VALVE1.LSW_SEL2: R60.2, TP39.1 (1_1), U19.10 (PF0)
VALVE1.~LSW_ST: R57.2, TP36.1 (1_1), U19.3 (PE4)
VALVE1_HSS_EN: R54.2, R56.2, TP34.1 (1_1), U19.1 (PE2)
VALVE1_LSS_EN: U10.4 (INB), U19.4 (PE5)
VALVE1_LSW_SNS: C48.1, R67.1, TP46.1 (1_1), U19.35 (PA1)
VALVE1_VSENSE_N: J6.1, R141.2, TP47.1 (1_1)
VALVE1_VSENSE_P: J6.2, R140.2, TP48.1 (1_1)
VALVE2.LSW_DIA_EN: R73.2, TP54.1 (1_1), U19.139 (PB8)
VALVE2.LSW_LATCH: R72.2, R190.2, TP53.1 (1_1), U19.135 (PB5)
VALVE2.LSW_SEL1: R75.2, TP56.1 (1_1), U19.141 (PE0)
VALVE2.LSW_SEL2: R74.2, TP55.1 (1_1), U19.140 (PB9)
VALVE2.~LSW_ST: R71.2, TP52.1 (1_1), U19.137 (PB7)
VALVE2_HSS_EN: R68.2, R70.2, TP50.1 (1_1), U19.136 (PB6)
VALVE2_LSS_EN: U10.2 (INA), U19.142 (PE1)
VALVE2_LSW_SNS: C53.1, R81.1, TP62.1 (1_1), U19.34 (PA0)
VALVE2_VSENSE_N: J7.1, R143.2, TP63.1 (1_1)
VALVE2_VSENSE_P: J7.2, R142.2, TP64.1 (1_1)
VALVE3.LSW_DIA_EN: R87.2, TP70.1 (1_1), U19.127 (PG12)
VALVE3.LSW_LATCH: R86.2, TP69.1 (1_1), U19.124 (PG9)
VALVE3.LSW_SEL1: R89.2, TP72.1 (1_1), U19.133 (PB3)
VALVE3.LSW_SEL2: R88.2, TP71.1 (1_1), U19.132 (PG15)
VALVE3.~LSW_ST: R85.2, TP68.1 (1_1), U19.126 (PG11)
VALVE3_HSS_EN: R82.2, R84.2, TP66.1 (1_1), U19.125 (PG10)
VALVE3_LSS_EN: U11.4 (INB), U19.134 (PB4)
VALVE3_LSW_SNS: C58.1, R95.1, TP78.1 (1_1), U19.29 (PC3)
VALVE3_VSENSE_N: J8.1, R145.2, TP79.1 (1_1)
VALVE3_VSENSE_P: J8.2, R144.2, TP80.1 (1_1)
VALVE4.LSW_DIA_EN: R101.2, TP86.1 (1_1), U19.118 (PD4)
VALVE4.LSW_LATCH: R100.2, TP85.1 (1_1), U19.114 (PD0)
VALVE4.LSW_SEL1: R103.2, TP88.1 (1_1), U19.122 (PD6)
VALVE4.LSW_SEL2: R102.2, TP87.1 (1_1), U19.119 (PD5)
VALVE4.~LSW_ST: R99.2, TP84.1 (1_1), U19.117 (PD3)
VALVE4_HSS_EN: R96.2, R98.2, TP82.1 (1_1), U19.115 (PD1)
VALVE4_LSS_EN: U11.2 (INA), U19.123 (PD7)
VALVE4_LSW_SNS: C63.1, R109.1, TP94.1 (1_1), U19.28 (PC2)
VALVE4_VSENSE_N: J9.1, R147.2, TP95.1 (1_1)
VALVE4_VSENSE_P: J9.2, R146.2, TP96.1 (1_1)
VALVE_GLOBAL_CTRL: R50.2, R51.2, R52.2, R53.2, U19.7 (PC13)
VBUS1: C17.1, C19.1, D3.2 (A), J23.4, J23.5, J23.6, Q4.1 (S), Q4.2 (S), Q4.3 (S), R24.2, TP187.1 (1_1), U7.6 (ANODE)
VBUS1_DISABLE: R20.2, U19.57 (PG1)
VBUS2: C18.1, C20.1, D4.2 (A), J22.4, J22.5, J22.6, Q3.1 (S), Q3.2 (S), Q3.3 (S), R25.2, TP185.1 (1_1), U6.6 (ANODE)
VBUS2_DISABLE: R22.2, U19.56 (PG0)
VBUS_VSENSE_N: NT1.2, R139.2
VBUS_VSENSE_P: C21.1, C22.1, C23.1, C24.1, C25.1, Q3.5 (D), Q4.5 (D), Q5.5 (D), R27.2, R29.2, R138.2, TP10.1 (1_1), U6.4 (CATHODE), U7.4 (CATHODE)
VSYS: C1.1, C2.1, C3.1, J20.1, R2.2, TP2.1 (1_1), U1.3 (VIN)
~ADC_CS: R175.1, U19.40 (PA4)
~ADC_DRDY: R179.1, U19.50 (PF12)
~ADC_RESET: R173.1, U19.46 (PB0)
~MAIN_RE: U19.48 (PB2), U23.4 (~RE)

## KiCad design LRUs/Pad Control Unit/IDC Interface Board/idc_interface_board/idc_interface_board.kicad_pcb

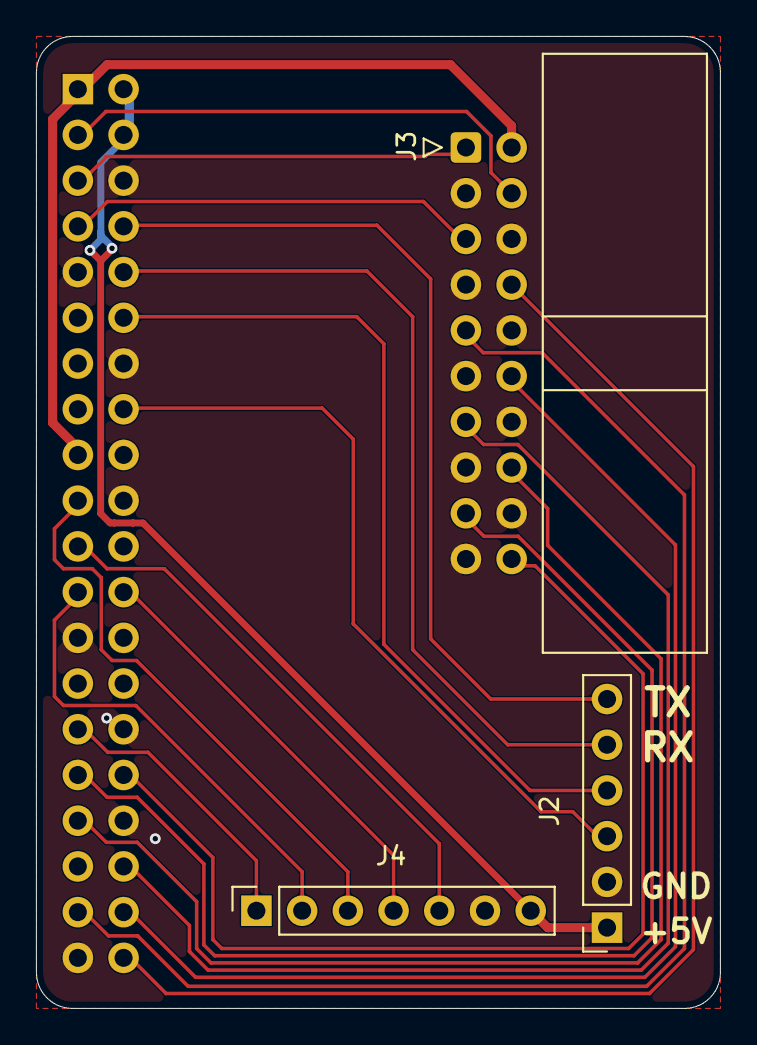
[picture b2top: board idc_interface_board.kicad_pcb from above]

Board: 2 copper layers, 38.0 x 54.0 mm, 4 parts (1 on the bottom side), 22 nets.

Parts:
J1: Conn_01x40; PinSocket_2x20_P2.54mm_Vertical
J2: Conn_01x06; PinSocket_1x06_P2.54mm_Vertical
J3: Conn_01x20; IDC-Header_2x10_P2.54mm_Horizontal
J4: Conn_01x07; PinSocket_1x07_P2.54mm_Vertical

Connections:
+3V3: J1.1, J1.17, J3.2
+5V: J1.2, J1.4, J2.1, J4.7
/Connectors/GPIO4: J1.7, J3.5
/Connectors/GPIO5: J1.29, J4.1
/Connectors/GPIO6: J1.31, J3.17
/Connectors/GPIO12: J1.32, J3.20
/Connectors/GPIO13: J1.33, J3.16
/Connectors/GPIO16: J1.36, J3.13
/Connectors/GPIO18: J1.12, J2.4
/Connectors/GPIO20: J1.38, J3.12
/Connectors/GPIO21: J1.40, J3.8
/Connectors/GPIO23: J1.16, J2.3
/Connectors/GPIO26: J1.37, J3.9
/Connectors/I2C1_SCL: J1.5, J3.1
/Connectors/I2C1_SDA: J1.3, J3.4
/Connectors/SPI0_CE0: J1.24, J4.4
/Connectors/SPI0_MISO: J1.21, J4.5
/Connectors/SPI0_MOSI: J1.19, J4.3
/Connectors/SPI0_SCLK: J1.23, J4.2
/Connectors/UART0_RX: J1.10, J2.5
/Connectors/UART0_TX: J1.8, J2.6
GND: J1.6, J1.9, J1.14, J1.20, J1.25, J1.30, J1.34, J1.39, J2.2, J3.3, J3.6, J3.7, J3.10, J3.11, J3.14, J3.15, J3.18, J3.19, J4.6
